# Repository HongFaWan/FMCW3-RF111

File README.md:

# FMCW3 RF111B · 619 位工程首板

这版六层主板用于 5.0–5.5 GHz 固定远距档 FMCW 验证，含一路发射和两路接收。每片实装 619 位，顶面 362 位、底面 257 位，共 198 个订货号。装配文件按一片计数。

| 用途 | 文件 |
| --- | --- |
| 查看和修改电路 | [KiCad 工程](hardware/fmcw3.kicad_pro) · [17 页原理图 PDF](manufacturing/RF111B_619_schematics.pdf) · [PCB](hardware/fmcw3.kicad_pcb) |
| 制板与电测 | [Gerber 和钻孔](manufacturing/gerbers) · [IPC-D-356A 裸板电测网表](manufacturing/ETest/RF111B_IPC-D-356A.d356) · [分层阻抗线路图](manufacturing/RF111B_619_impedance.pdf) |
| 逐孔工艺 | [30 处指定填孔盖铜](manufacturing/03A_必须填盖孔.csv) · [163 处开孔或条件复核](manufacturing/03B_开孔和条件复核.csv) · [制造与装配说明](manufacturing/制造与装配说明.md) |
| 贴片与装配核对 | [双面贴装坐标](manufacturing/RF111B_619_CPL_mm.csv) · [有方向元件定位](manufacturing/RF111B_有方向元件辅助定位.csv) · [免采购位与默认铜桥](manufacturing/RF111B_免采购位与默认铜桥.csv) |
| 采购 | [619 位逐件 BOM](procurement/BOM_RF111B_619.csv) · [198 组订货号、备选和采购渠道](procurement/RF111B_198_采购渠道.csv) |
| 上电与版本核对 | [USB 首次配置](hardware/USB首次配置.md) · [逐文件 SHA-256](SHA256SUMS) · [上游归属](SOURCE_CREDITS.txt) · [许可](LICENSE) |

用 KiCad 10.0.8 打开工程并保留 `hardware/libraries` 的相对位置。采购表的数量为单板净用量，起订量和贴装损耗按选用供应商另计。淘宝店铺及商品标题只在原号或已核包装号相符时列出。下单时核对完整型号、包装、批次及实际可交付数量。

## 首板上电

对应固件为 **FW101-619R2**。首次限流上电用 `RF111B_619_FW101_bringup.bit`，该镜像将 PA_EN 保持为低。混频器和采集在使能条件稳定后共等待 409.6 µs。临时标定用 `RF111B_619_CAL_JTAG_ONLY.bit`。每片的工作镜像使用该板的实测标定数据生成。

| 对象 | SHA-256 |
| --- | --- |
| 本版 PCB | `a31ce20355b4fa4a97ab1be27c61c8bd2aee6932014cd293fbca63f2d87f8769` |
| 首板上电 .bit | `9f23ade9e8424474dfdef7c0eb7f3b96057b2d42a69f1a3f6b118c192e5e65d3` |
| JTAG 标定 .bit | `038ec09d5bfff4f78416c5b02aa63c316596a4f46cf53e25bf58e2a450170f9a` |

当前分支用于首板打样。合并主分支前，需在实板核实固定档本振两端余量、PA 与 U22 装壳温升、U29 冷启动及掉电恢复，并完成双通道回波采集。

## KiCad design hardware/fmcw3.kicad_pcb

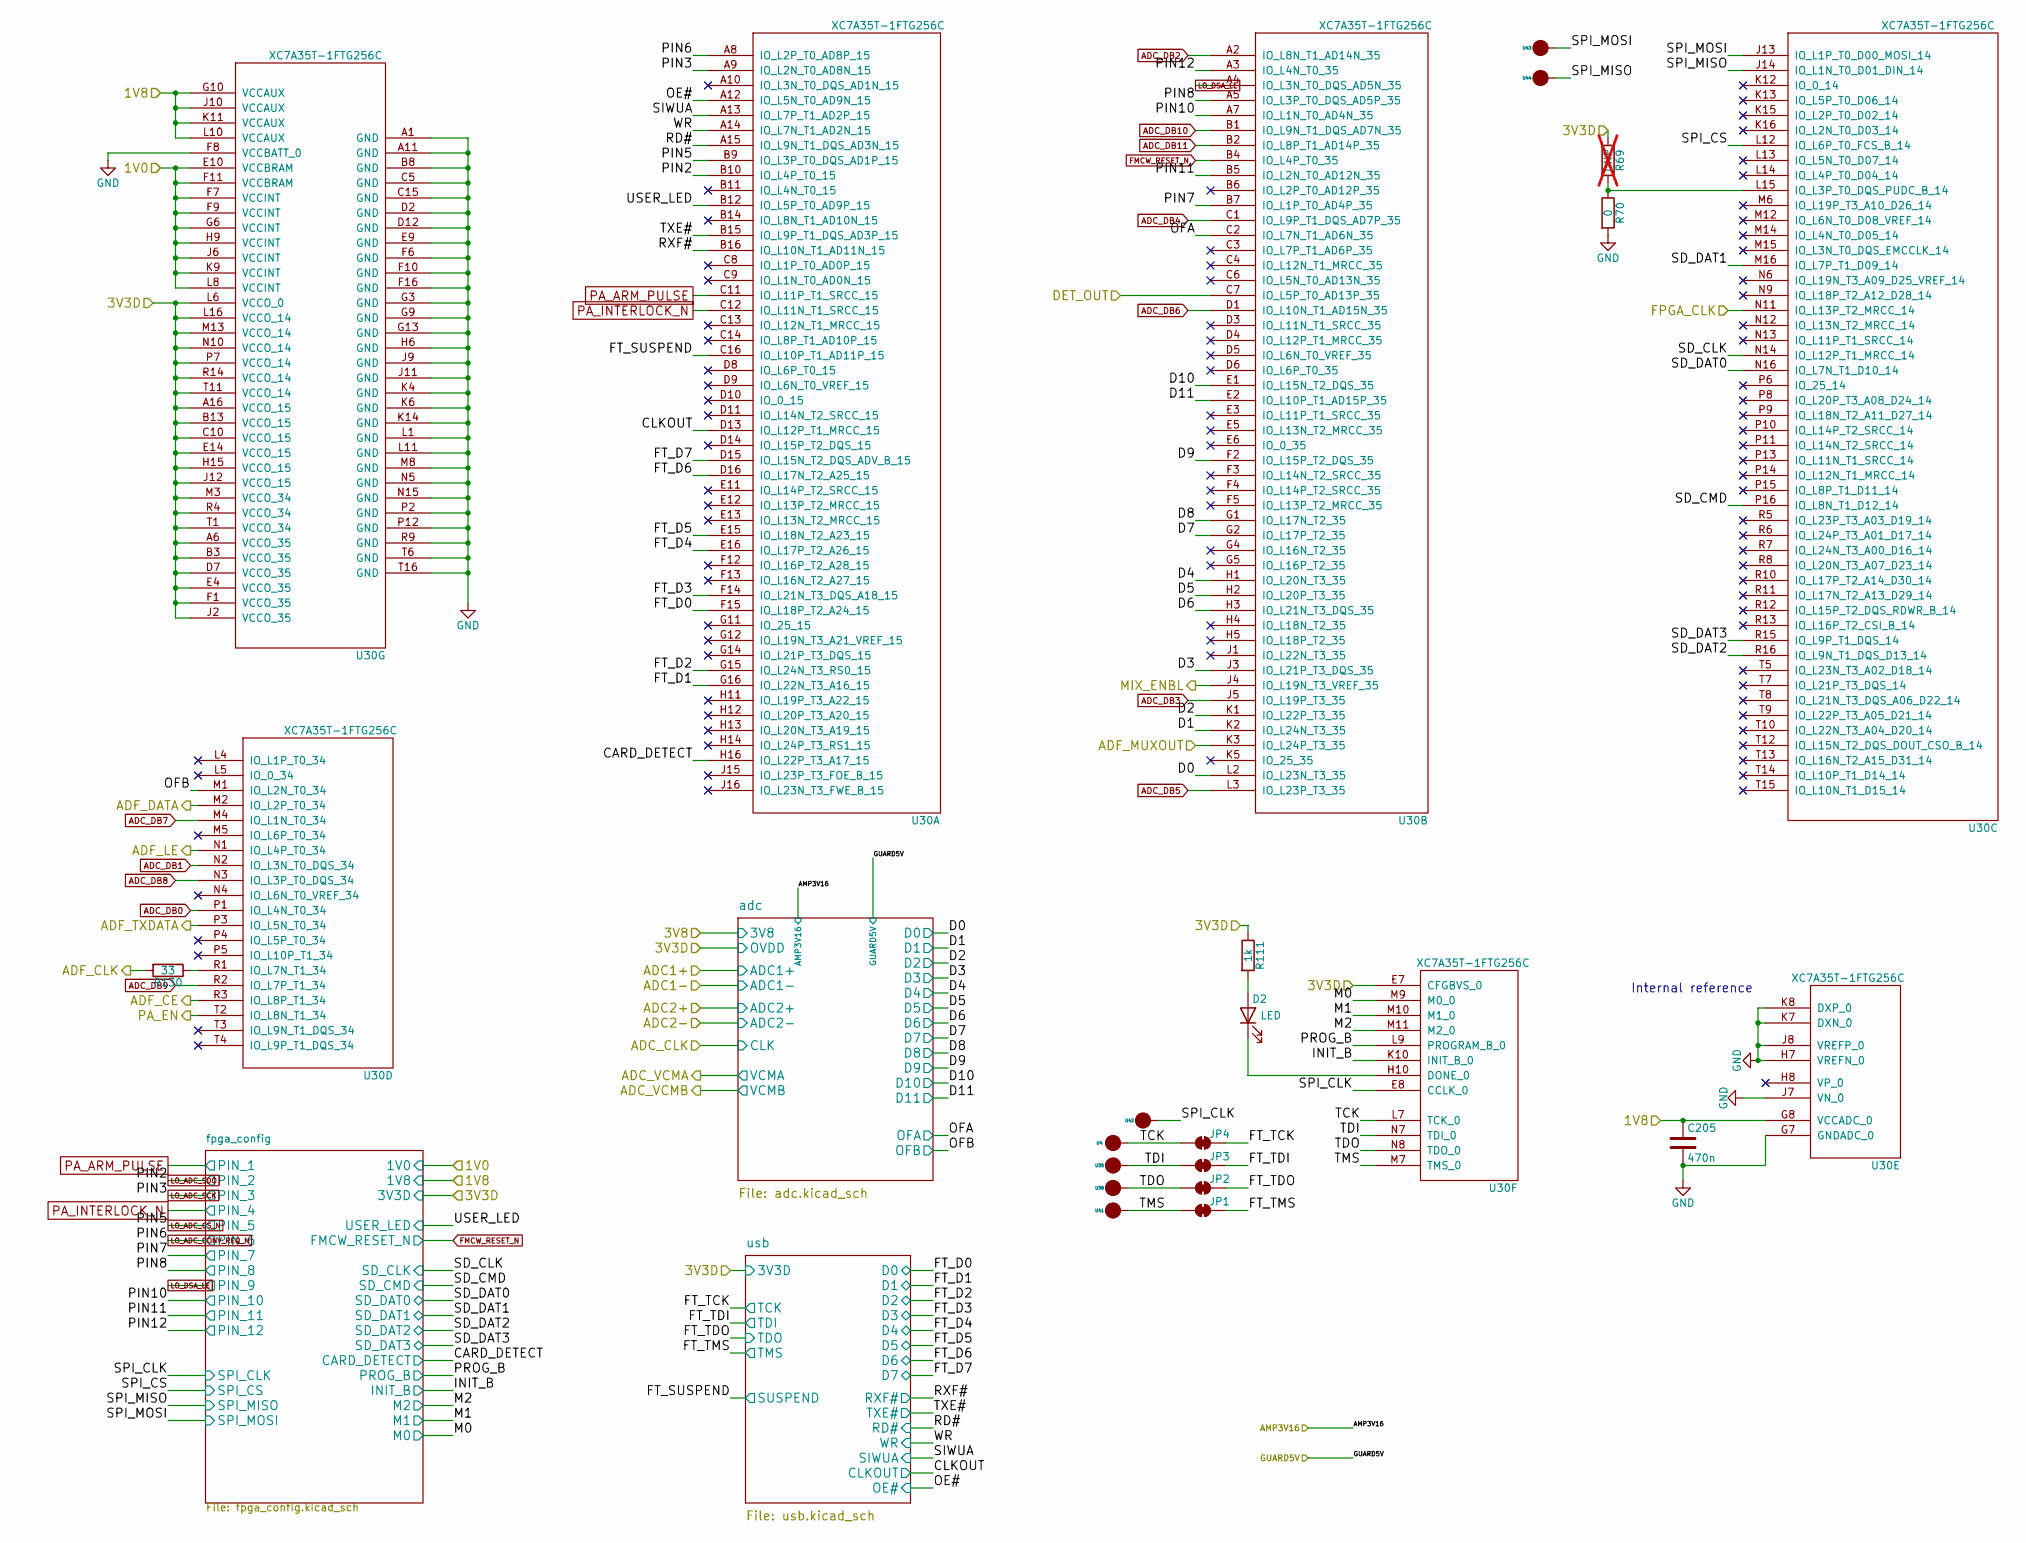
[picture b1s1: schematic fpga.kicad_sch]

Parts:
C205: 470n; SMD_0402
D2: LED; Diode_0603
JP1, JP2, JP3, JP4: SolderJumper_2_Bridged; SolderPad_2_Bridge
R69: DNP; SMD_0402; not fitted
R70: 0; SMD_0402
R111: 1k; SMD_0402
R130: 33; SMD_0402
U4, U35, U38, U41, U42, U43, U44: SolderPad_1_Circle; SolderPad_1_1.0mm_SMD_Circle
U30: XC7A35T-1FTG256C; FTG256

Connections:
/1V0: U30.E10 (VCCBRAM), U30.F7 (VCCINT), U30.F9 (VCCINT), U30.F11 (VCCBRAM), U30.G6 (VCCINT), U30.H9 (VCCINT), U30.J6 (VCCINT), U30.K9 (VCCINT), U30.L8 (VCCINT); also elsewhere on the board
/1V8: C205.1, U30.G8 (VCCADC_0), U30.G10 (VCCAUX), U30.J10 (VCCAUX), U30.K11 (VCCAUX), U30.L10 (VCCAUX); also elsewhere on the board
/ADF_CE: U30.R3 (IO_L8P_T1_34); also elsewhere on the board
/ADF_CLK: R130.2; also elsewhere on the board
/ADF_DATA: U30.M2 (IO_L2P_T0_34); also elsewhere on the board
/ADF_LE: U30.N1 (IO_L4P_T0_34); also elsewhere on the board
/ADF_MUXOUT: U30.K3 (IO_L24P_T3_35); also elsewhere on the board
/ADF_TXDATA: U30.P3 (IO_L5N_T0_34); also elsewhere on the board
/DET_OUT: U30.C7 (IO_L5P_T0_AD13P_35); also elsewhere on the board
/FPGA_CLK: U30.N11 (IO_L13P_T2_MRCC_14); also elsewhere on the board
/MIX_ENBL: U30.J4 (IO_L19N_T3_VREF_35); also elsewhere on the board
/PA_EN: U30.T2 (IO_L8N_T1_34); also elsewhere on the board
/fpga/CARD_DETECT: U30.H16 (IO_L22P_T3_A17_15); also elsewhere on the board
/fpga/CLKOUT: U30.D13 (IO_L12P_T1_MRCC_15); also elsewhere on the board
/fpga/D0: U30.L2 (IO_L23N_T3_35); also elsewhere on the board
/fpga/D1: U30.K2 (IO_L24N_T3_35); also elsewhere on the board
/fpga/D2: U30.K1 (IO_L22P_T3_35); also elsewhere on the board
/fpga/D3: U30.J3 (IO_L21P_T3_DQS_35); also elsewhere on the board
/fpga/D4: U30.H1 (IO_L20N_T3_35); also elsewhere on the board
/fpga/D5: U30.H2 (IO_L20P_T3_35); also elsewhere on the board
/fpga/D6: U30.H3 (IO_L21N_T3_DQS_35); also elsewhere on the board
/fpga/D7: U30.G2 (IO_L17P_T2_35); also elsewhere on the board
/fpga/D8: U30.G1 (IO_L17N_T2_35); also elsewhere on the board
/fpga/D9: U30.F2 (IO_L15P_T2_DQS_35); also elsewhere on the board
/fpga/D10: U30.E1 (IO_L15N_T2_DQS_35); also elsewhere on the board
/fpga/D11: U30.E2 (IO_L10P_T1_AD15P_35); also elsewhere on the board
/fpga/FT_D0: U30.F15 (IO_L18P_T2_A24_15); also elsewhere on the board
/fpga/FT_D1: U30.G16 (IO_L22N_T3_A16_15); also elsewhere on the board
/fpga/FT_D2: U30.G15 (IO_L24N_T3_RS0_15); also elsewhere on the board
/fpga/FT_D3: U30.F14 (IO_L21N_T3_DQS_A18_15); also elsewhere on the board
/fpga/FT_D4: U30.E16 (IO_L17P_T2_A26_15); also elsewhere on the board
/fpga/FT_D5: U30.E15 (IO_L18N_T2_A23_15); also elsewhere on the board
/fpga/FT_D6: U30.D16 (IO_L17N_T2_A25_15); also elsewhere on the board
/fpga/FT_D7: U30.D15 (IO_L15N_T2_DQS_ADV_B_15); also elsewhere on the board
/fpga/FT_SUSPEND: U30.C16 (IO_L10P_T1_AD11P_15); also elsewhere on the board
/fpga/FT_TCK: JP4.2 (B); also elsewhere on the board
/fpga/FT_TDI: JP3.2 (B); also elsewhere on the board
/fpga/FT_TDO: JP2.2 (B); also elsewhere on the board
/fpga/FT_TMS: JP1.2 (B); also elsewhere on the board
/fpga/INIT_B: U30.K10 (INIT_B_0); also elsewhere on the board
/fpga/M0: U30.M9 (M0_0); also elsewhere on the board
/fpga/M1: U30.M10 (M1_0); also elsewhere on the board
/fpga/M2: U30.M11 (M2_0); also elsewhere on the board
/fpga/OE#: U30.A12 (IO_L5N_T0_AD9N_15); also elsewhere on the board
/fpga/OFA: U30.C2 (IO_L7N_T1_AD6N_35); also elsewhere on the board
/fpga/OFB: U30.M1 (IO_L2N_T0_34); also elsewhere on the board
/fpga/PIN7: U30.B7 (IO_L1P_T0_AD4P_35); also elsewhere on the board
/fpga/PIN8: U30.A5 (IO_L3P_T0_DQS_AD5P_35); also elsewhere on the board
/fpga/PIN10: U30.A7 (IO_L1N_T0_AD4N_35); also elsewhere on the board
/fpga/PIN11: U30.B5 (IO_L2N_T0_AD12N_35); also elsewhere on the board
/fpga/PIN12: U30.A3 (IO_L4N_T0_35); also elsewhere on the board
/fpga/PROG_B: U30.L9 (PROGRAM_B_0); also elsewhere on the board
/fpga/RD#: U30.A15 (IO_L9N_T1_DQS_AD3N_15); also elsewhere on the board
/fpga/RXF#: U30.B16 (IO_L10N_T1_AD11N_15); also elsewhere on the board
/fpga/SD_CLK: U30.N14 (IO_L12P_T1_MRCC_14); also elsewhere on the board
/fpga/SD_CMD: U30.P16 (IO_L8N_T1_D12_14); also elsewhere on the board
/fpga/SD_DAT0: U30.N16 (IO_L7N_T1_D10_14); also elsewhere on the board
/fpga/SD_DAT1: U30.M16 (IO_L7P_T1_D09_14); also elsewhere on the board
/fpga/SD_DAT2: U30.R16 (IO_L9N_T1_DQS_D13_14); also elsewhere on the board
/fpga/SD_DAT3: U30.R15 (IO_L9P_T1_DQS_14); also elsewhere on the board
/fpga/SIWUA: U30.A13 (IO_L7P_T1_AD2P_15); also elsewhere on the board
/fpga/SPI_CLK: U30.E8 (CCLK_0), U42.1; also elsewhere on the board
/fpga/SPI_CS: U30.L12 (IO_L6P_T0_FCS_B_14); also elsewhere on the board
/fpga/SPI_MISO: U30.J14 (IO_L1N_T0_D01_DIN_14), U44.1; also elsewhere on the board
/fpga/SPI_MOSI: U30.J13 (IO_L1P_T0_D00_MOSI_14), U43.1; also elsewhere on the board
/fpga/TCK: JP4.1 (A), U4.1, U30.L7 (TCK_0)
/fpga/TDI: JP3.1 (A), U30.N7 (TDI_0), U35.1
/fpga/TDO: JP2.1 (A), U30.N8 (TDO_0), U38.1
/fpga/TMS: JP1.1 (A), U30.M7 (TMS_0), U41.1
/fpga/TXE#: U30.B15 (IO_L9P_T1_DQS_AD3P_15); also elsewhere on the board
/fpga/USER_LED: U30.B12 (IO_L5P_T0_AD9P_15); also elsewhere on the board
/fpga/WR: U30.A14 (IO_L7N_T1_AD2N_15); also elsewhere on the board
ADC_DB0: U30.P1 (IO_L4N_T0_34); also elsewhere on the board
ADC_DB1: U30.N2 (IO_L3N_T0_DQS_34); also elsewhere on the board
ADC_DB2: U30.A2 (IO_L8N_T1_AD14N_35); also elsewhere on the board
ADC_DB3: U30.J5 (IO_L19P_T3_35); also elsewhere on the board
ADC_DB4: U30.C1 (IO_L9P_T1_DQS_AD7P_35); also elsewhere on the board
ADC_DB5: U30.L3 (IO_L23P_T3_35); also elsewhere on the board
ADC_DB6: U30.D1 (IO_L10N_T1_AD15N_35); also elsewhere on the board
ADC_DB7: U30.M4 (IO_L1N_T0_34); also elsewhere on the board
ADC_DB8: U30.N3 (IO_L3P_T0_DQS_34); also elsewhere on the board
ADC_DB9: U30.R2 (IO_L7P_T1_34); also elsewhere on the board
ADC_DB10: U30.B1 (IO_L9N_T1_DQS_AD7N_35); also elsewhere on the board
ADC_DB11: U30.B2 (IO_L8P_T1_AD14P_35); also elsewhere on the board
FMCW_RESET_N: U30.B4 (IO_L4P_T0_35); also elsewhere on the board
GND: C205.2, R70.2, U30.A1 (GND), U30.A11 (GND), U30.B8 (GND), U30.C5 (GND), U30.C15 (GND), U30.D2 (GND), U30.D12 (GND), U30.E9 (GND), U30.F6 (GND), U30.F8 (VCCBATT_0), U30.F10 (GND), U30.F16 (GND), U30.G3 (GND), U30.G7 (GNDADC_0), U30.G9 (GND), U30.G13 (GND), U30.H6 (GND), U30.H7 (VREFN_0), U30.J7 (VN_0), U30.J8 (VREFP_0), U30.J9 (GND), U30.J11 (GND), U30.K4 (GND), U30.K6 (GND), U30.K7 (DXN_0), U30.K8 (DXP_0), U30.K14 (GND), U30.L1 (GND), U30.L11 (GND), U30.M8 (GND), U30.N5 (GND), U30.N15 (GND), U30.P2 (GND), U30.P12 (GND), U30.R9 (GND), U30.T6 (GND), U30.T16 (GND); also elsewhere on the board
LO_ADC_CONV_REQ_N: U30.A8 (IO_L2P_T0_AD8P_15); also elsewhere on the board
LO_ADC_CS_N: U30.B9 (IO_L3P_T0_DQS_AD1P_15); also elsewhere on the board
LO_ADC_SCK: U30.A9 (IO_L2N_T0_AD8N_15); also elsewhere on the board
LO_ADC_SDO: U30.B10 (IO_L4P_T0_15); also elsewhere on the board
LO_DSA_LE: U30.A4 (IO_L3N_T0_DQS_AD5N_35); also elsewhere on the board
unnamed: D2.2 (A), R111.2
unnamed: D2.1 (K), U30.H10 (DONE_0)
unnamed: R69.2, R70.1, U30.L15 (IO_L3P_T0_DQS_PUDC_B_14)
unnamed: R130.1, U30.R1 (IO_L7N_T1_34)
PA_ARM_PULSE: U30.C11 (IO_L11P_T1_SRCC_15); also elsewhere on the board
PA_INTERLOCK_N: U30.C12 (IO_L11N_T1_SRCC_15); also elsewhere on the board

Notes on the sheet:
Internal reference
